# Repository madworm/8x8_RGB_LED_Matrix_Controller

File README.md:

8x8_RGB_LED_Matrix_Controller
=============================

LAYOUT FILES: 8x8-RGB-LED-Matrix controller using 4x 74HC595 shift registers. CPU: ATmega168/328. Arduino 'compatible'. Runs with code from [V3_x_boards_test](https://github.com/madworm/V3_x_boards_test) repo. KICAD and Gerber files.

---

Before having PC-boards made, please make sure you know about your manufacturer's peculiarities!
Especially drill-sizes and their tolerances may vary too much and give you trouble.

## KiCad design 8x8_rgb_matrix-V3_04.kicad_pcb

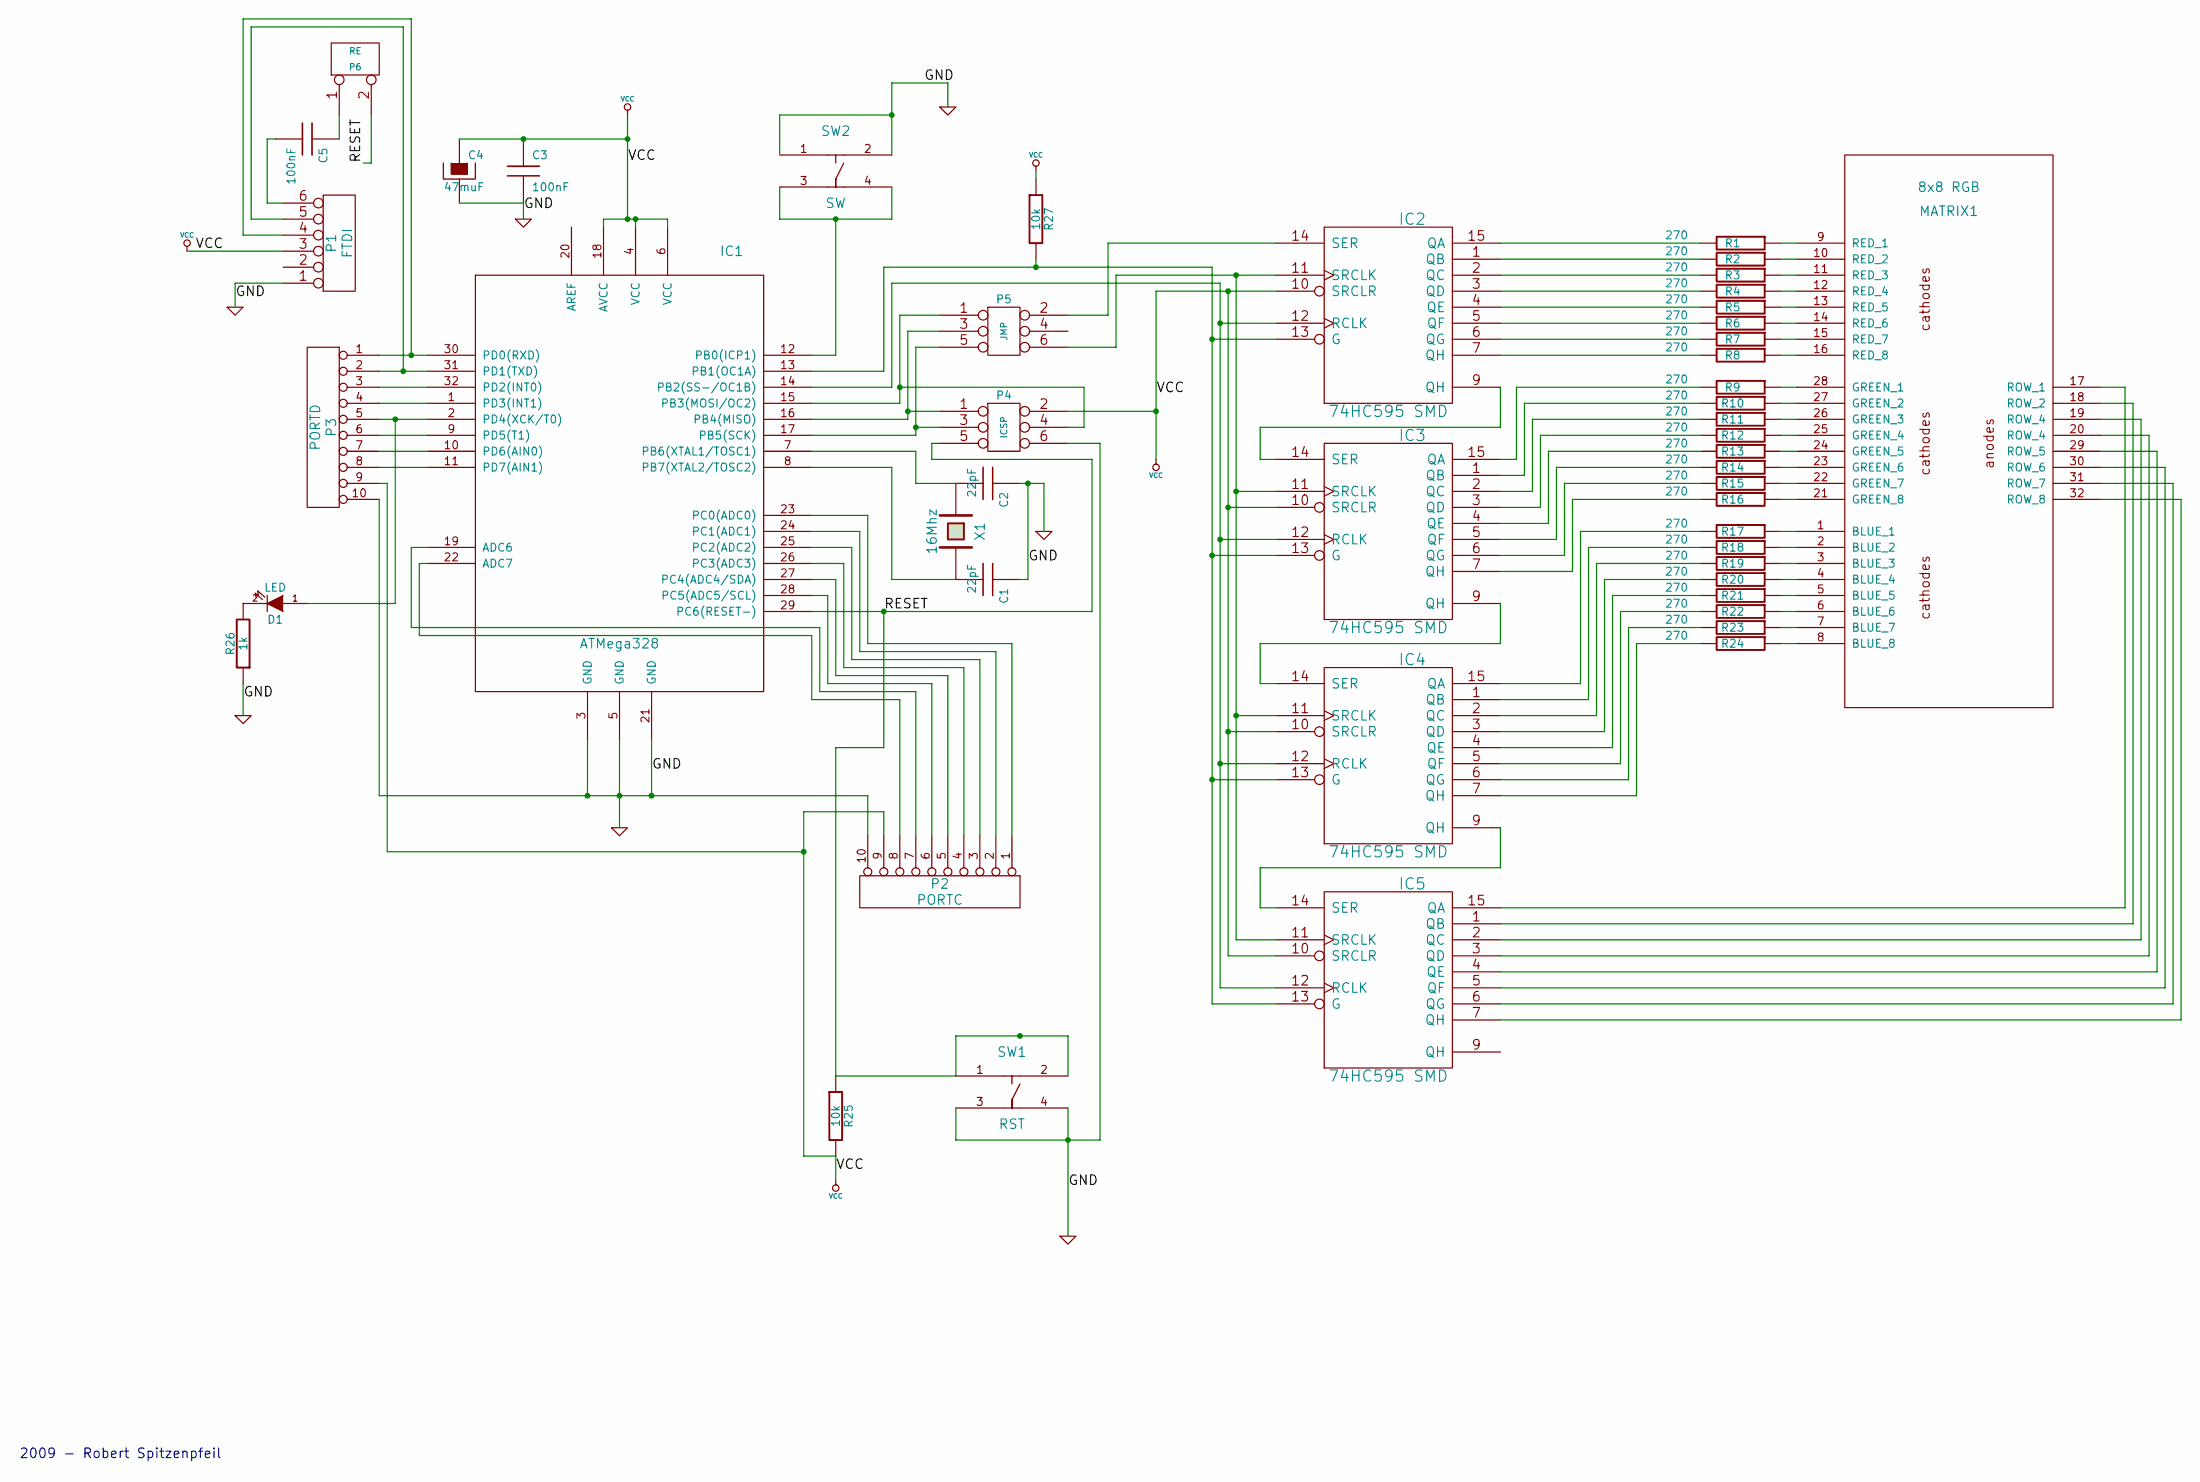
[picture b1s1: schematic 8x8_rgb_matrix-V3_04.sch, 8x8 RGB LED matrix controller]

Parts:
C1, C2: 22pF
C3, C5: 100nF
C4: 47muF
D1: LED
IC1: ATMega328
IC2, IC3, IC4, IC5: 74HC595 SMD
MATRIX1: 8x8 RGB
P1: FTDI
P2: PORTC
P3: PORTD
P4: ICSP
P5: JMP
P6: RE
R1, R2, R3, R4, R5, R6, R7, R8, R9, R10, R11, R12, R13, R14, R15, R16, R17, R18, R19, R20, R21, R22, R23, R24: 270
R25, R27: 10k
R26: 1k
SW1: RST
SW2: SW
X1: 16Mhz

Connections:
/GND: C1.1, C2.1, C3.2, C4.2, IC1.3 (GND), IC1.5 (GND), IC1.21 (GND), IC2.8 (GND), IC3.8 (GND), IC4.8 (GND), IC5.8 (GND), P1.1, P2.10, P3.10, P4.6, R26.1, SW1.3, SW1.4, SW2.1, SW2.2
/RESET: IC1.29 (PC6(RESET-)), P4.5, P6.2 (PM), R25.1, SW1.1, SW1.2
unnamed: IC1.16 (PB4(MISO)), P4.1, P5.3
unnamed: IC1.30 (PD0(RXD)), P1.4, P3.1
unnamed: C5.1, P6.1
unnamed: C5.2, P1.6
unnamed: C1.2, IC1.8 (PB7(XTAL2/TOSC2)), X1.2
unnamed: IC1.28 (PC5(ADC5/SCL)), P2.6
unnamed: IC1.26 (PC3(ADC3)), P2.4
unnamed: IC1.24 (PC1(ADC1)), P2.2
unnamed: IC2.14 (SER), P5.2
unnamed: IC1.22 (ADC7), P2.8
unnamed: IC1.19 (ADC6), P2.7
unnamed: D1.1 (A), IC1.2 (PD4(XCK/T0)), P3.5
unnamed: IC1.11 (PD7(AIN1)), P3.8
unnamed: IC1.9 (PD5(T1)), P3.6
unnamed: IC1.1 (PD3(INT1)), P3.4
unnamed: IC5.7 (QH), MATRIX1.32 (ROW_8)
unnamed: IC5.5 (QF), MATRIX1.30 (ROW_6)
unnamed: IC5.3 (QD), MATRIX1.20 (ROW_4)
unnamed: IC5.1 (QB), MATRIX1.18 (ROW_2)
unnamed: IC2.7 (QH), R8.2
unnamed: IC2.5 (QF), R6.2
unnamed: IC2.3 (QD), R4.2
unnamed: IC2.1 (QB), R2.2
unnamed: IC3.15 (QA), R9.2
unnamed: IC3.2 (QC), R11.2
unnamed: IC3.4 (QE), R13.2
unnamed: IC3.6 (QG), R15.2
unnamed: MATRIX1.8 (BLUE_8), R24.1
unnamed: MATRIX1.6 (BLUE_6), R22.1
unnamed: MATRIX1.4 (BLUE_4), R20.1
unnamed: MATRIX1.2 (BLUE_2), R18.1
unnamed: MATRIX1.21 (GREEN_8), R16.1
unnamed: MATRIX1.23 (GREEN_6), R14.1
unnamed: MATRIX1.25 (GREEN_4), R12.1
unnamed: MATRIX1.27 (GREEN_2), R10.1
unnamed: MATRIX1.16 (RED_8), R8.1
unnamed: MATRIX1.14 (RED_6), R6.1
unnamed: MATRIX1.12 (RED_4), R4.1
unnamed: MATRIX1.10 (RED_2), R2.1
unnamed: IC4.9 (QH), IC5.14 (SER)
unnamed: IC4.6 (QG), R23.2
unnamed: IC4.4 (QE), R21.2
unnamed: IC4.2 (QC), R19.2
unnamed: IC4.15 (QA), R17.2
unnamed: IC3.7 (QH), R16.2
unnamed: IC2.9 (QH), IC3.14 (SER)
unnamed: IC3.1 (QB), R10.2
unnamed: IC3.3 (QD), R12.2
unnamed: IC3.5 (QF), R14.2
unnamed: IC3.9 (QH), IC4.14 (SER)
unnamed: IC4.1 (QB), R18.2
unnamed: IC4.3 (QD), R20.2
unnamed: IC4.5 (QF), R22.2
unnamed: IC4.7 (QH), R24.2
unnamed: MATRIX1.9 (RED_1), R1.1
unnamed: MATRIX1.11 (RED_3), R3.1
unnamed: MATRIX1.13 (RED_5), R5.1
unnamed: MATRIX1.15 (RED_7), R7.1
unnamed: MATRIX1.28 (GREEN_1), R9.1
unnamed: MATRIX1.26 (GREEN_3), R11.1
unnamed: MATRIX1.24 (GREEN_5), R13.1
unnamed: MATRIX1.22 (GREEN_7), R15.1
unnamed: MATRIX1.1 (BLUE_1), R17.1
unnamed: MATRIX1.3 (BLUE_3), R19.1
unnamed: MATRIX1.5 (BLUE_5), R21.1
unnamed: MATRIX1.7 (BLUE_7), R23.1
unnamed: IC2.15 (QA), R1.2
unnamed: IC2.2 (QC), R3.2
unnamed: IC2.4 (QE), R5.2
unnamed: IC2.6 (QG), R7.2
unnamed: IC5.15 (QA), MATRIX1.17 (ROW_1)
unnamed: IC5.2 (QC), MATRIX1.19 (ROW_4)
unnamed: IC5.4 (QE), MATRIX1.29 (ROW_5)
unnamed: IC5.6 (QG), MATRIX1.31 (ROW_7)
unnamed: IC1.31 (PD1(TXD)), P1.5, P3.2
unnamed: IC1.32 (PD2(INT0)), P3.3
unnamed: IC1.10 (PD6(AIN0)), P3.7
unnamed: IC1.15 (PB3(MOSI/OC2)), P4.4, P5.1
unnamed: IC1.14 (PB2(SS-/OC1B)), IC2.12 (RCLK), IC3.12 (RCLK), IC4.12 (RCLK), IC5.12 (RCLK)
unnamed: IC2.11 (SRCLK), IC3.11 (SRCLK), IC4.11 (SRCLK), IC5.11 (SRCLK), P5.6
unnamed: IC1.17 (PB5(SCK)), P4.3, P5.5
unnamed: IC1.13 (PB1(OC1A)), IC2.13 (G), IC3.13 (G), IC4.13 (G), IC5.13 (G), R27.2
unnamed: IC1.12 (PB0(ICP1)), SW2.3, SW2.4
unnamed: IC1.23 (PC0(ADC0)), P2.1
unnamed: IC1.25 (PC2(ADC2)), P2.3
unnamed: IC1.27 (PC4(ADC4/SDA)), P2.5
unnamed: C2.2, IC1.7 (PB6(XTAL1/TOSC1)), X1.1
unnamed: D1.2 (K), R26.2
VCC: C3.1, C4.1, IC1.4 (VCC), IC1.6 (VCC), IC1.18 (AVCC), IC2.10 (SRCLR), IC2.16 (VCC), IC3.10 (SRCLR), IC3.16 (VCC), IC4.10 (SRCLR), IC4.16 (VCC), IC5.10 (SRCLR), IC5.16 (VCC), P1.3, P2.9, P3.9, P4.2, R25.2, R27.1

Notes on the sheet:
2009 - Robert Spitzenpfeil

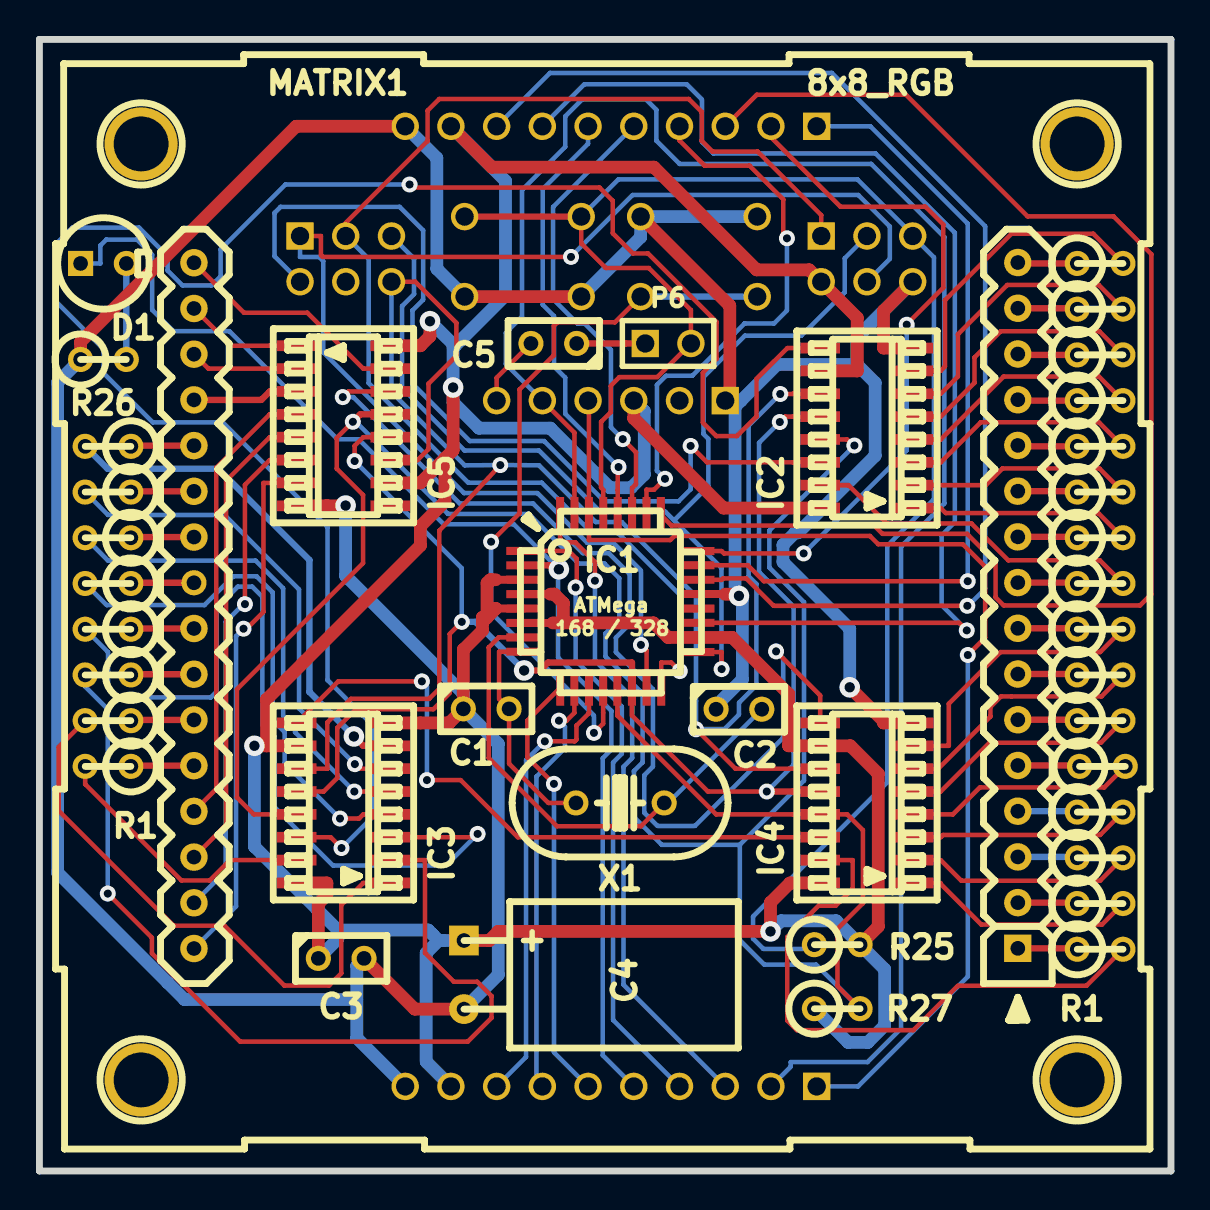
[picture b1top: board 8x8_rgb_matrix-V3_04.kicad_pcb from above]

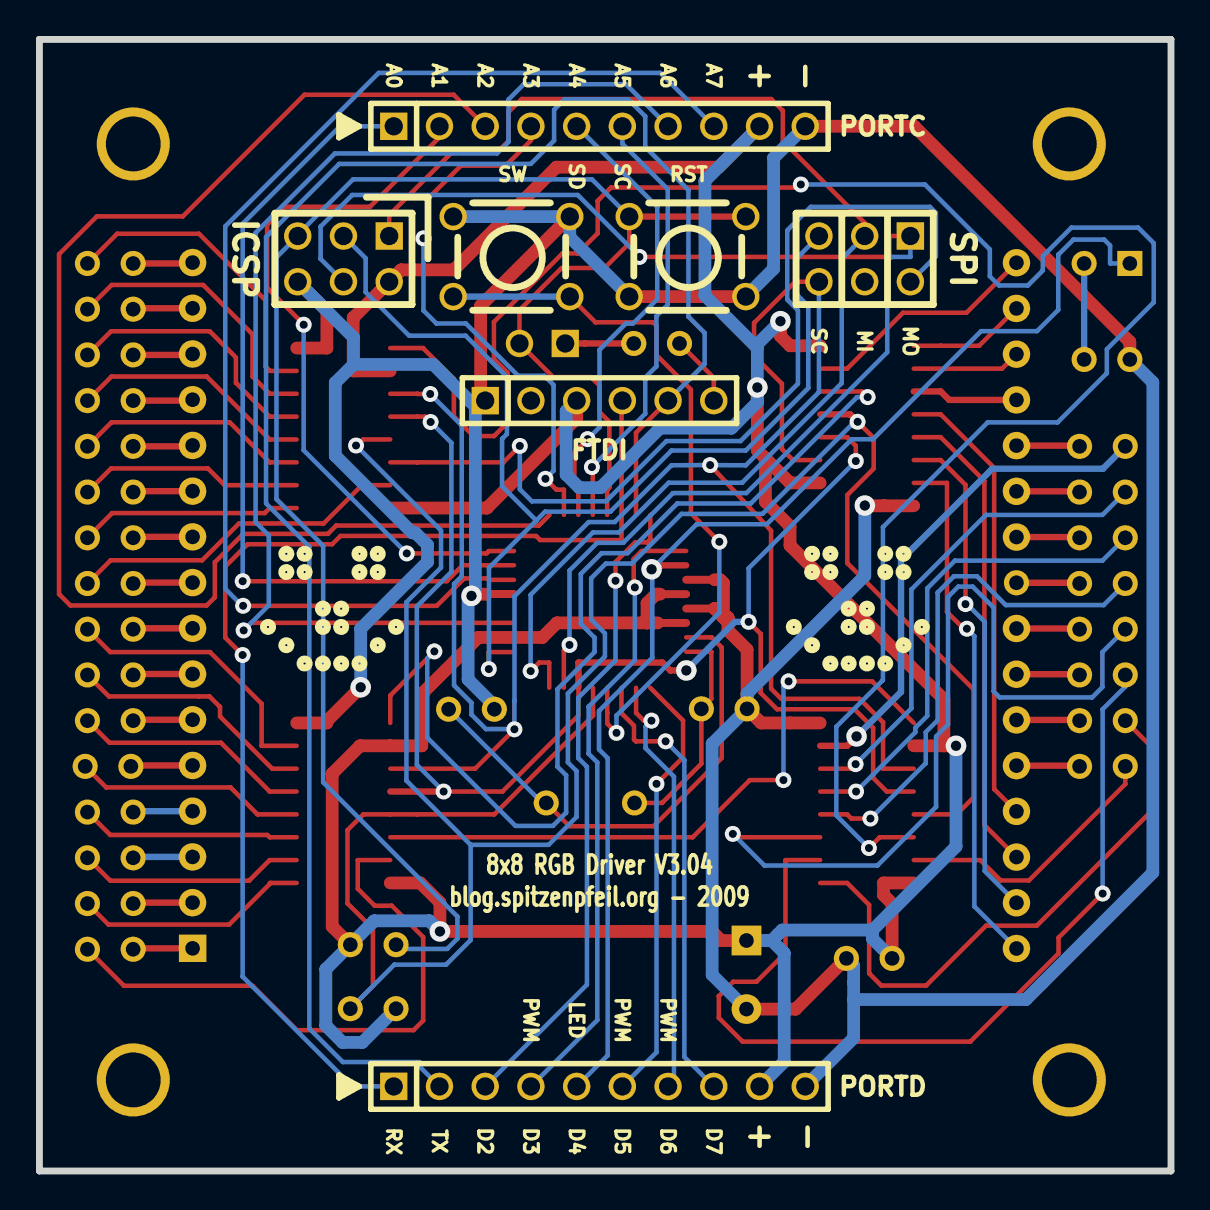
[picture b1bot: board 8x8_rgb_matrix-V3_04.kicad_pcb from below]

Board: 2 copper layers, 62.9 x 62.9 mm, 52 parts (7 on the bottom side), 91 nets.

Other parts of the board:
1PIN-1, 1PIN-2, 1PIN-3, 1PIN-4: P***; 1pin

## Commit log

2011-06-06 Added the assembly manual (pdf) and a link to the code repo.
2011-10-05 Renamed the schematic files for consistency reasons.
2012-04-06 Added 'push.sh'
2012-06-02 Finally added .gitignore to the repo.
2012-06-02 Removed files now covered by .gitignore
2012-06-02 Updated .gitignore
2012-09-03 Cleaned up the .gvp files...
2013-01-17 Added README.md
2013-01-23 Changed library path, so it doesn't use a symlink anymore.
2013-01-25 Increased drill size for pin-headers to 40mil + recreated gerber files.
    Had to redo some of the routing due to clearance issues. Now it conforms
    to 8mil clearances. Also some of the auto-router traces were insane...
2013-06-28 Converted to new kicad board format.
2014-11-26 Schematic fixed (pwr_flags, no-connects...) & LED-matrix (pins to passive).
    All layout-related files unchanged.
2015-01-09 Added hyperlink to firmware repo.
